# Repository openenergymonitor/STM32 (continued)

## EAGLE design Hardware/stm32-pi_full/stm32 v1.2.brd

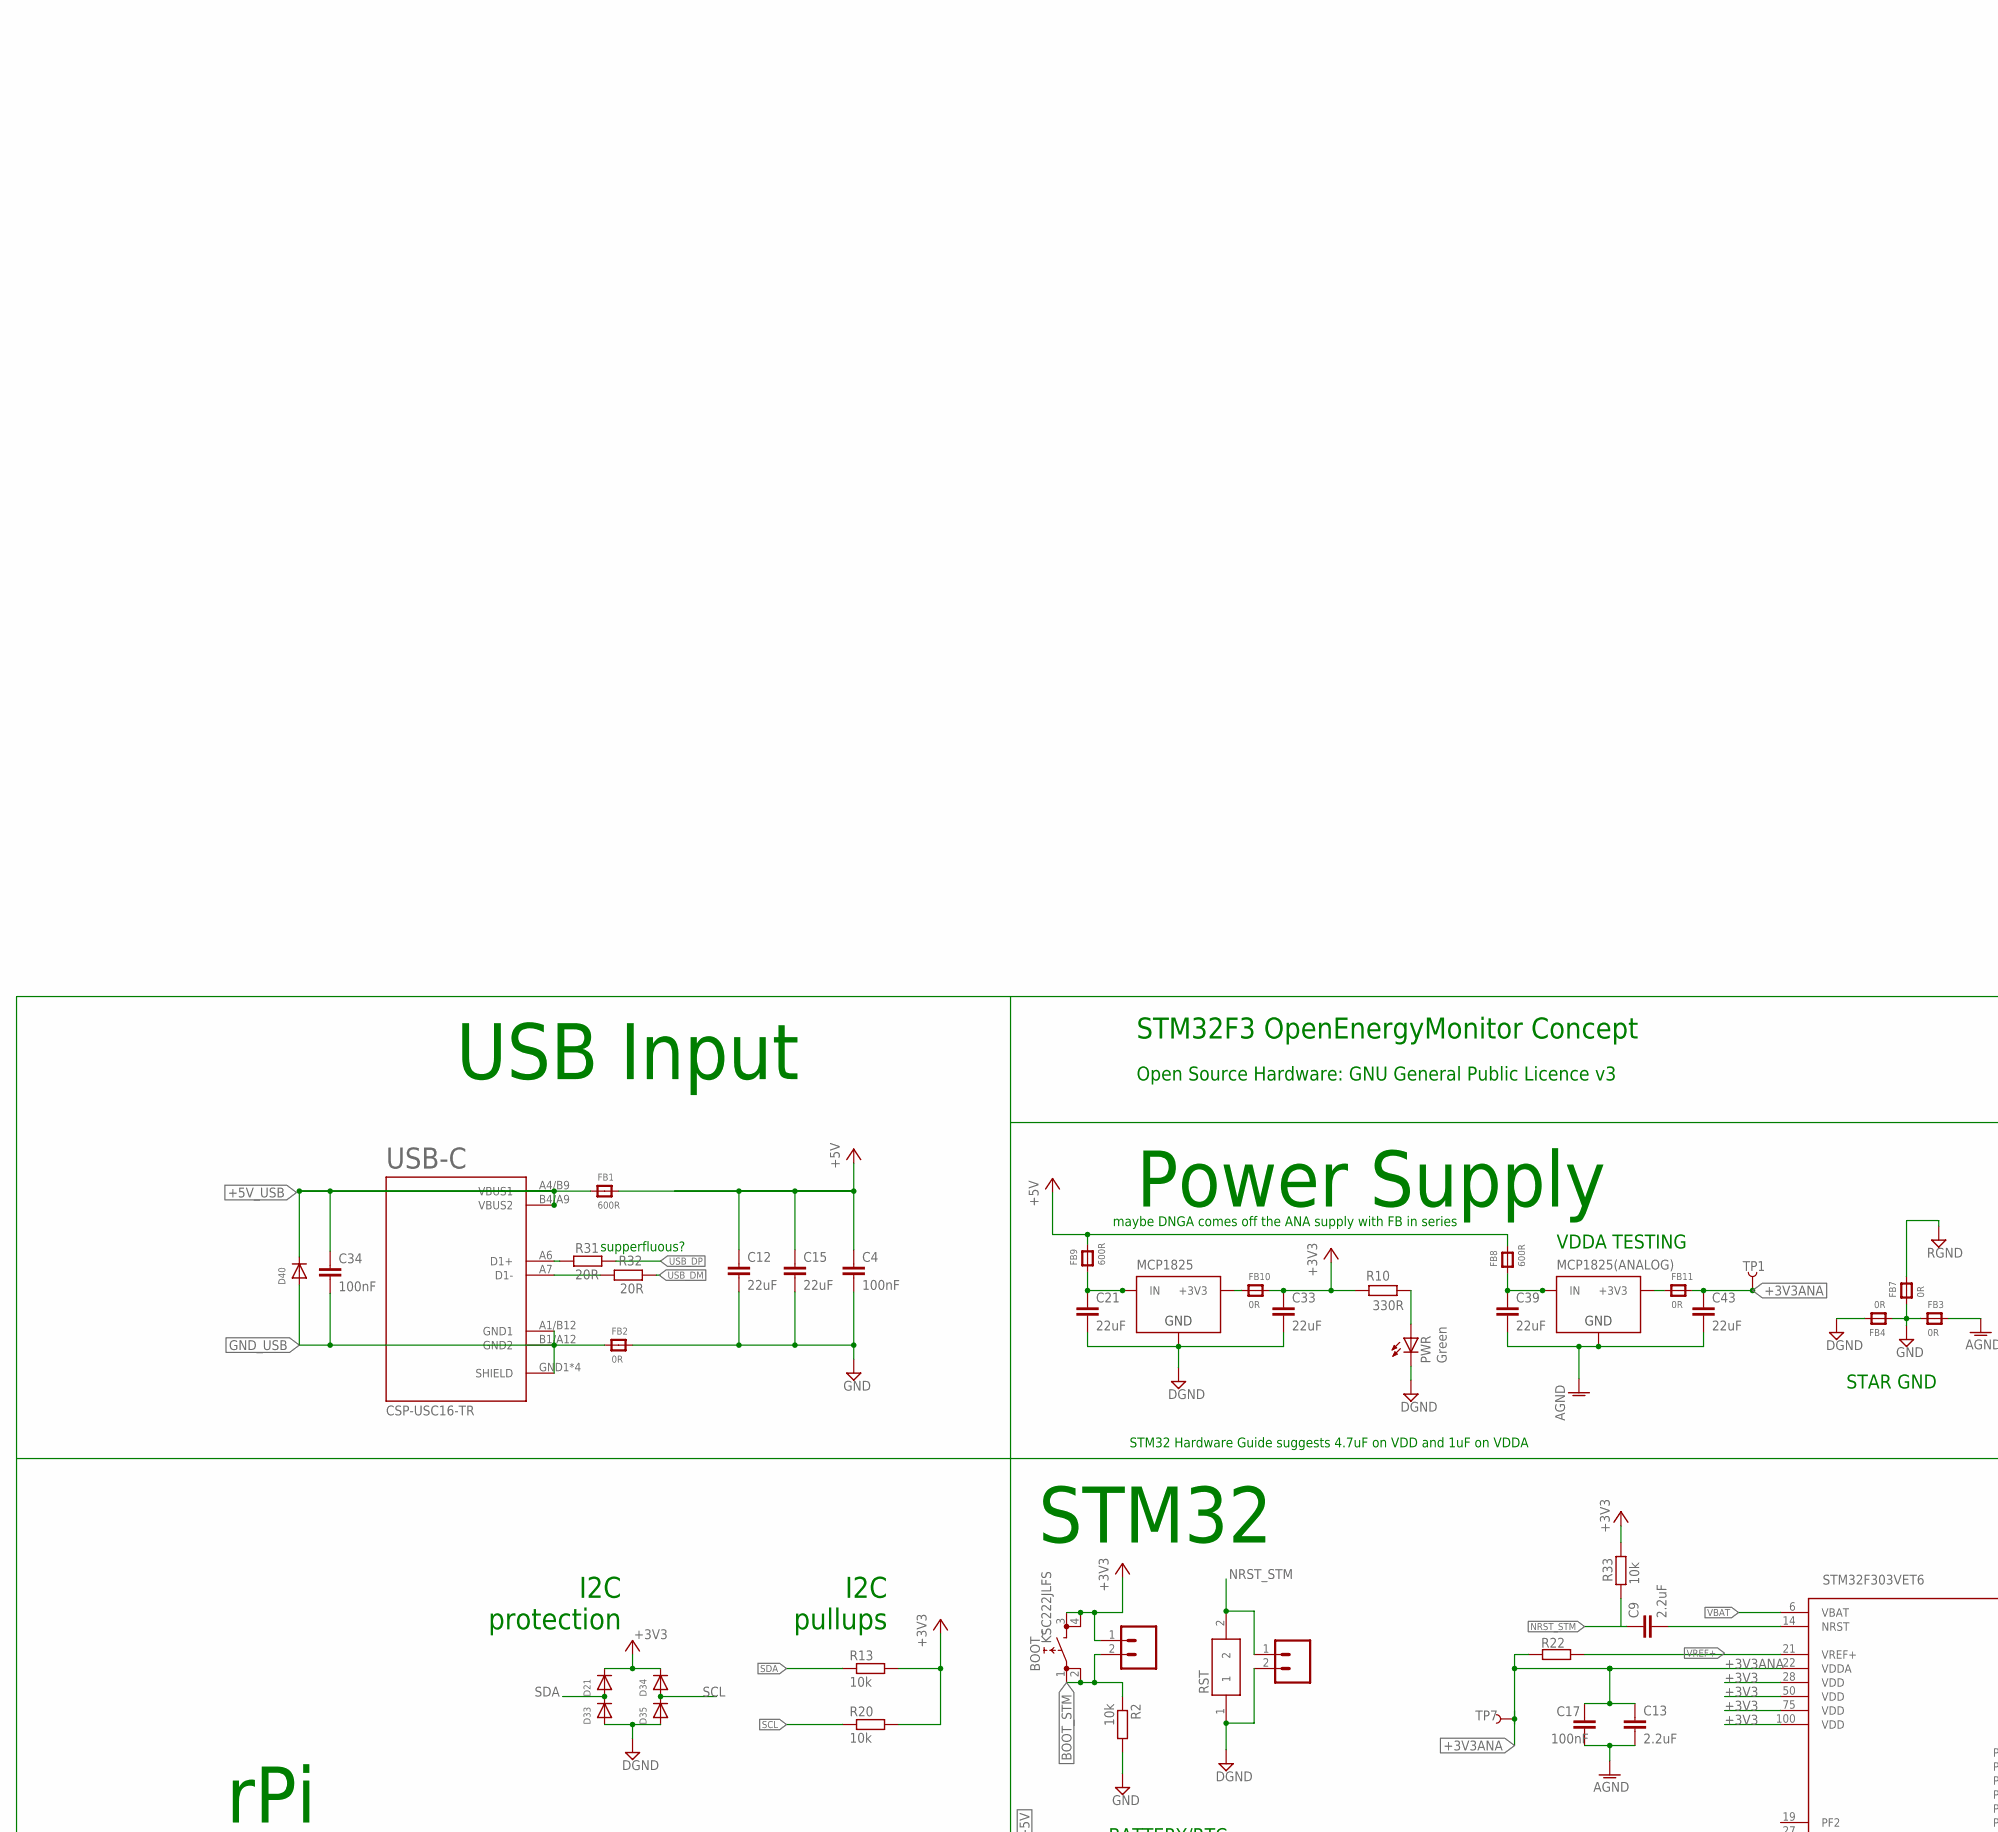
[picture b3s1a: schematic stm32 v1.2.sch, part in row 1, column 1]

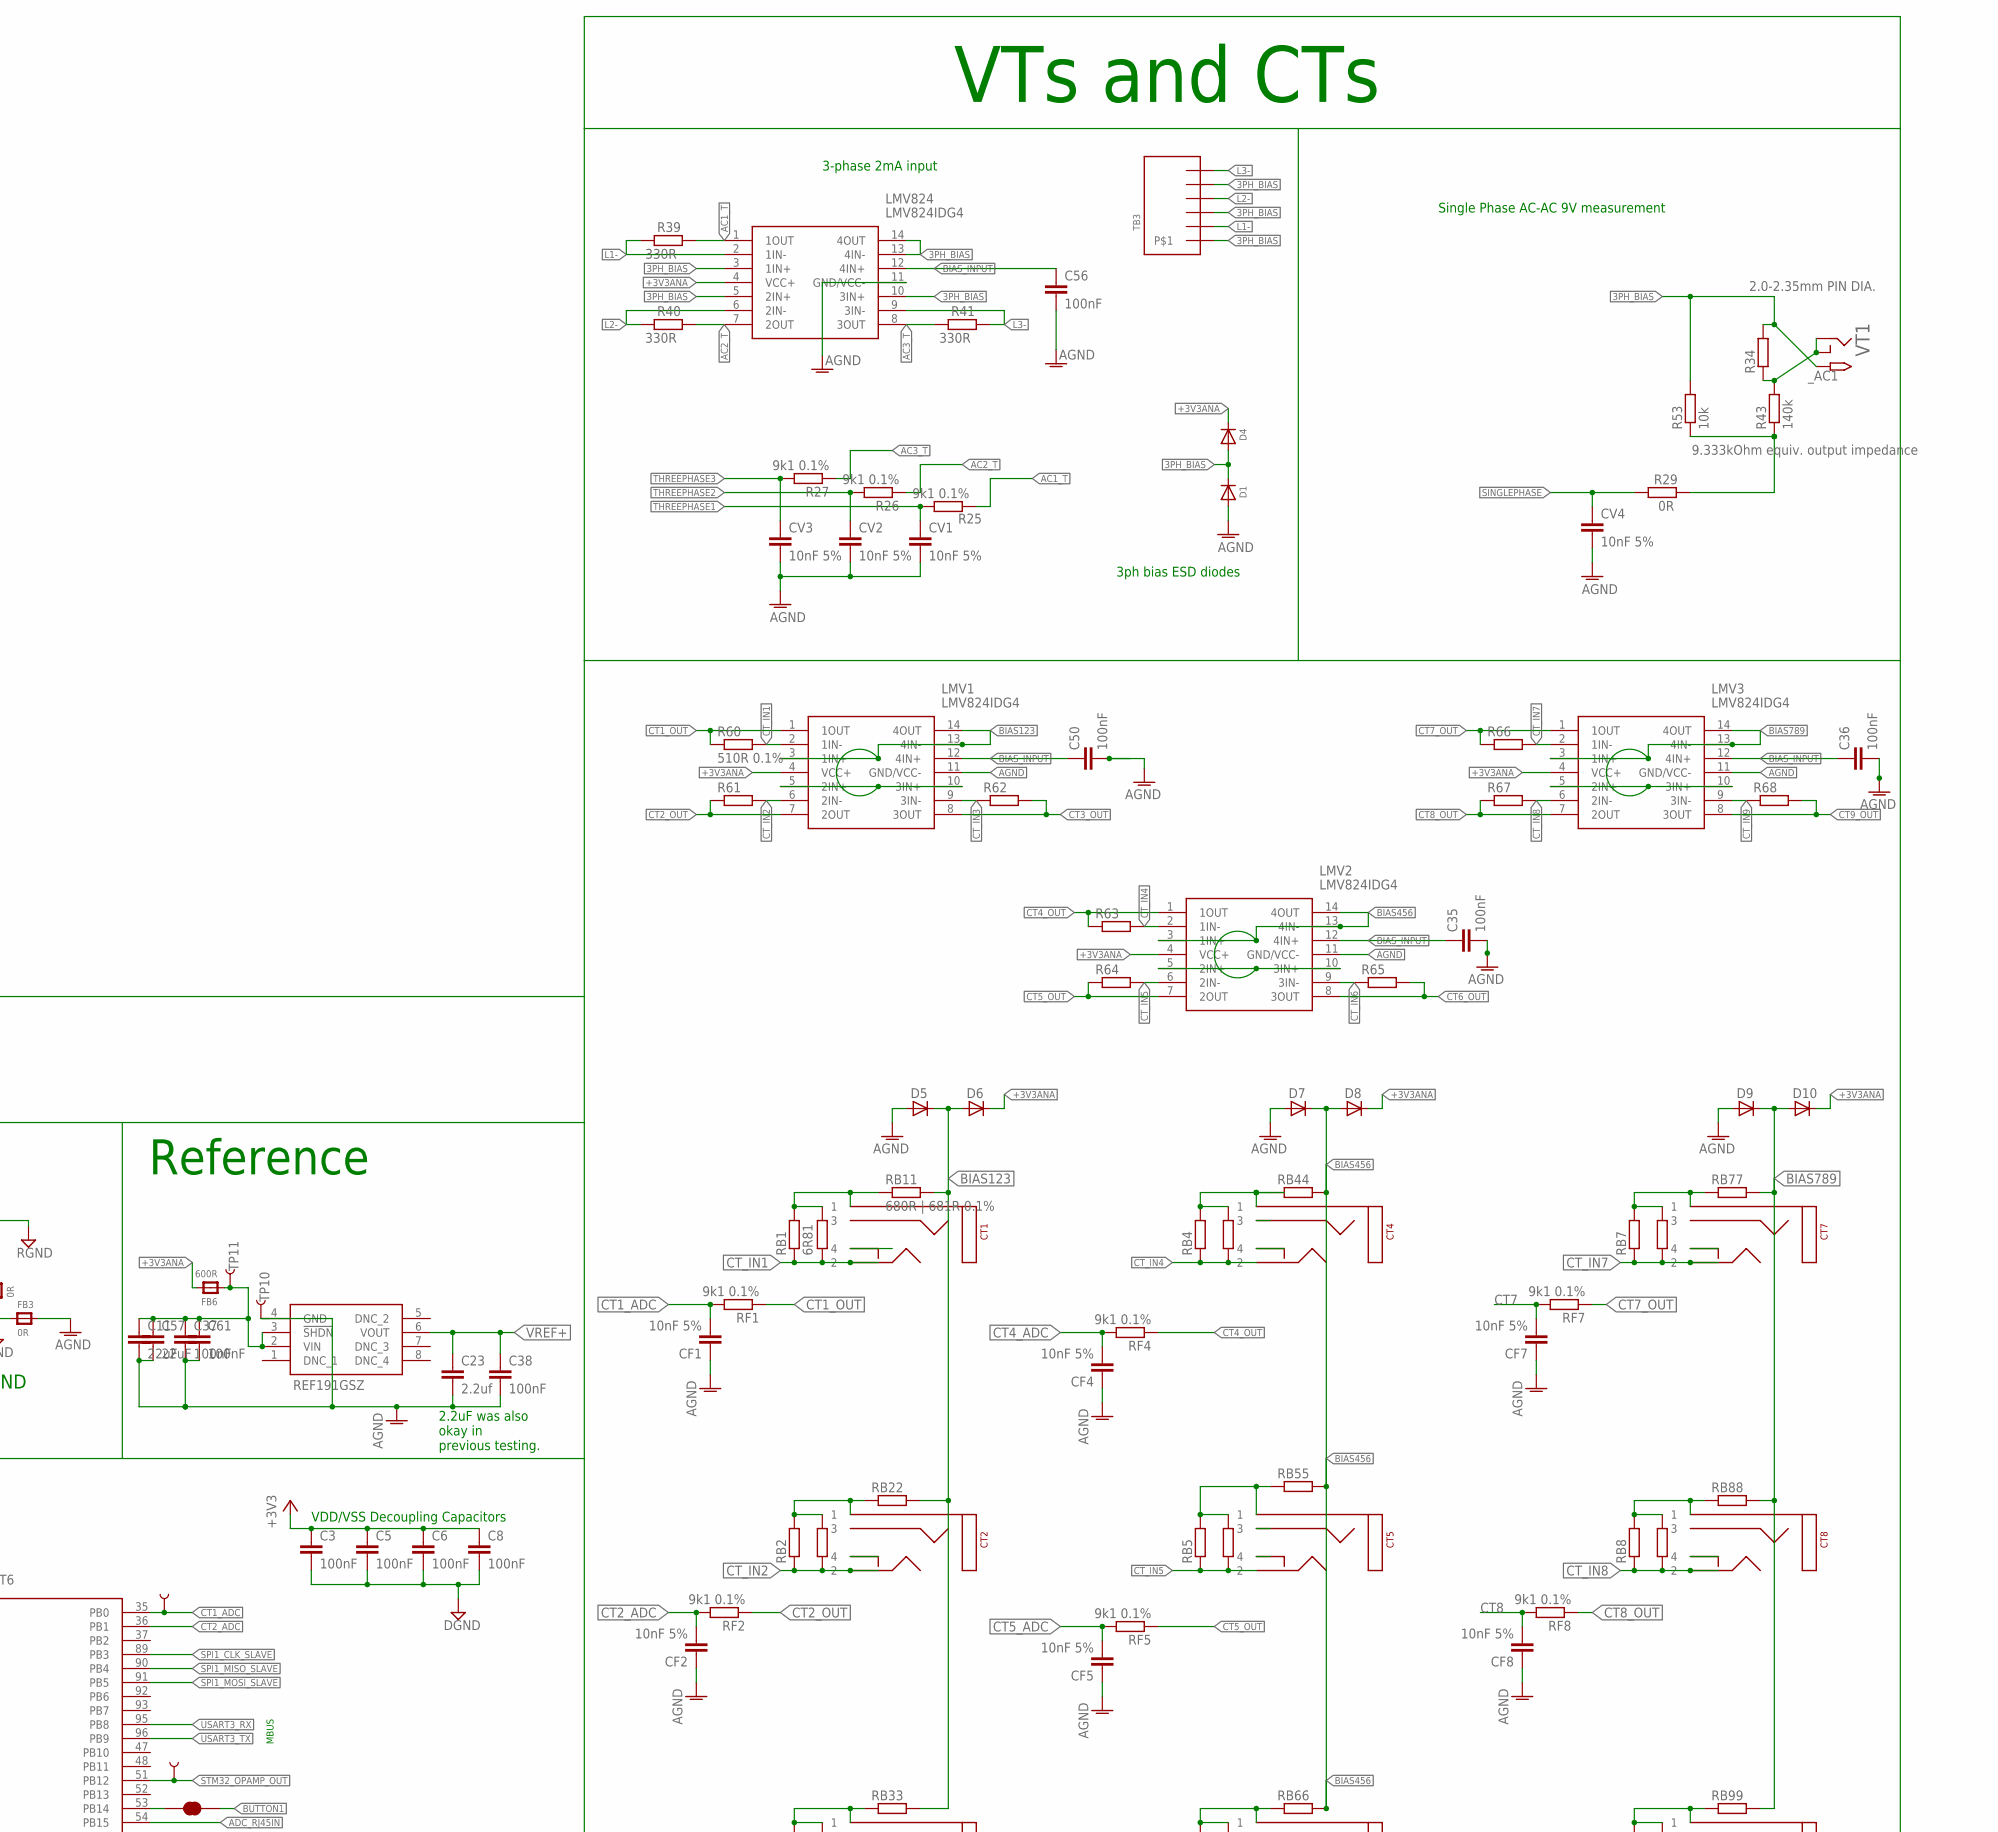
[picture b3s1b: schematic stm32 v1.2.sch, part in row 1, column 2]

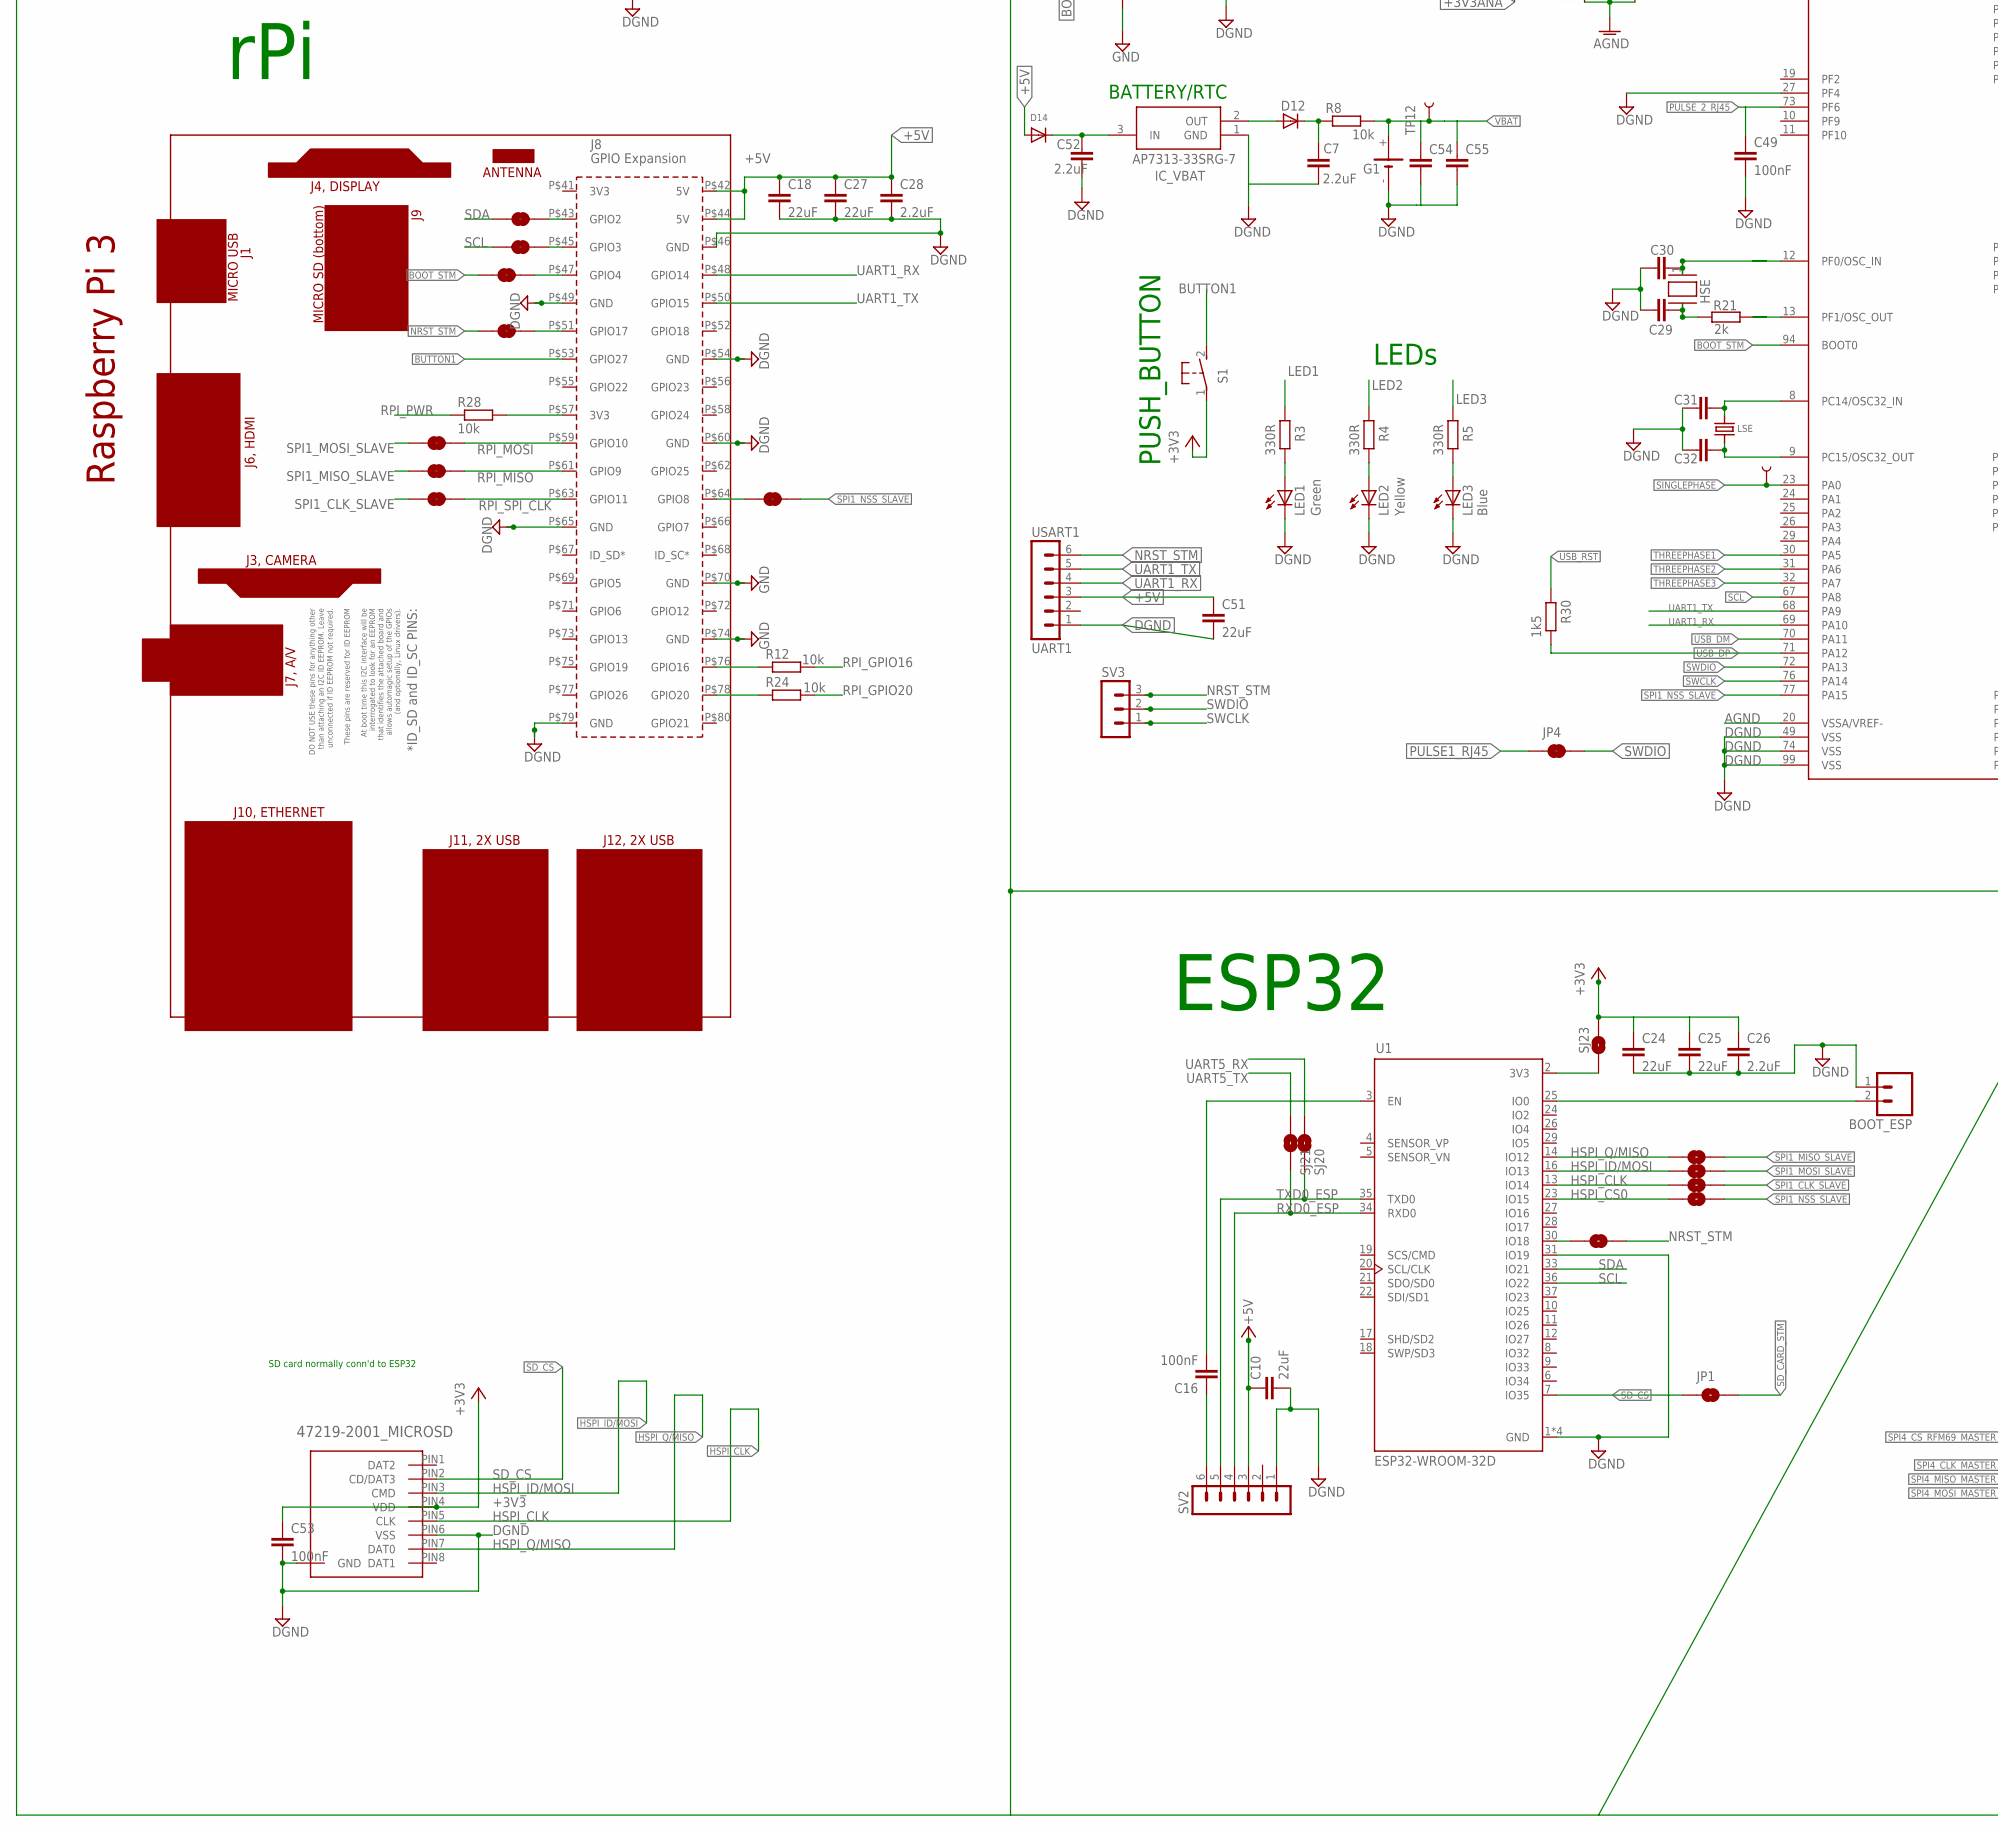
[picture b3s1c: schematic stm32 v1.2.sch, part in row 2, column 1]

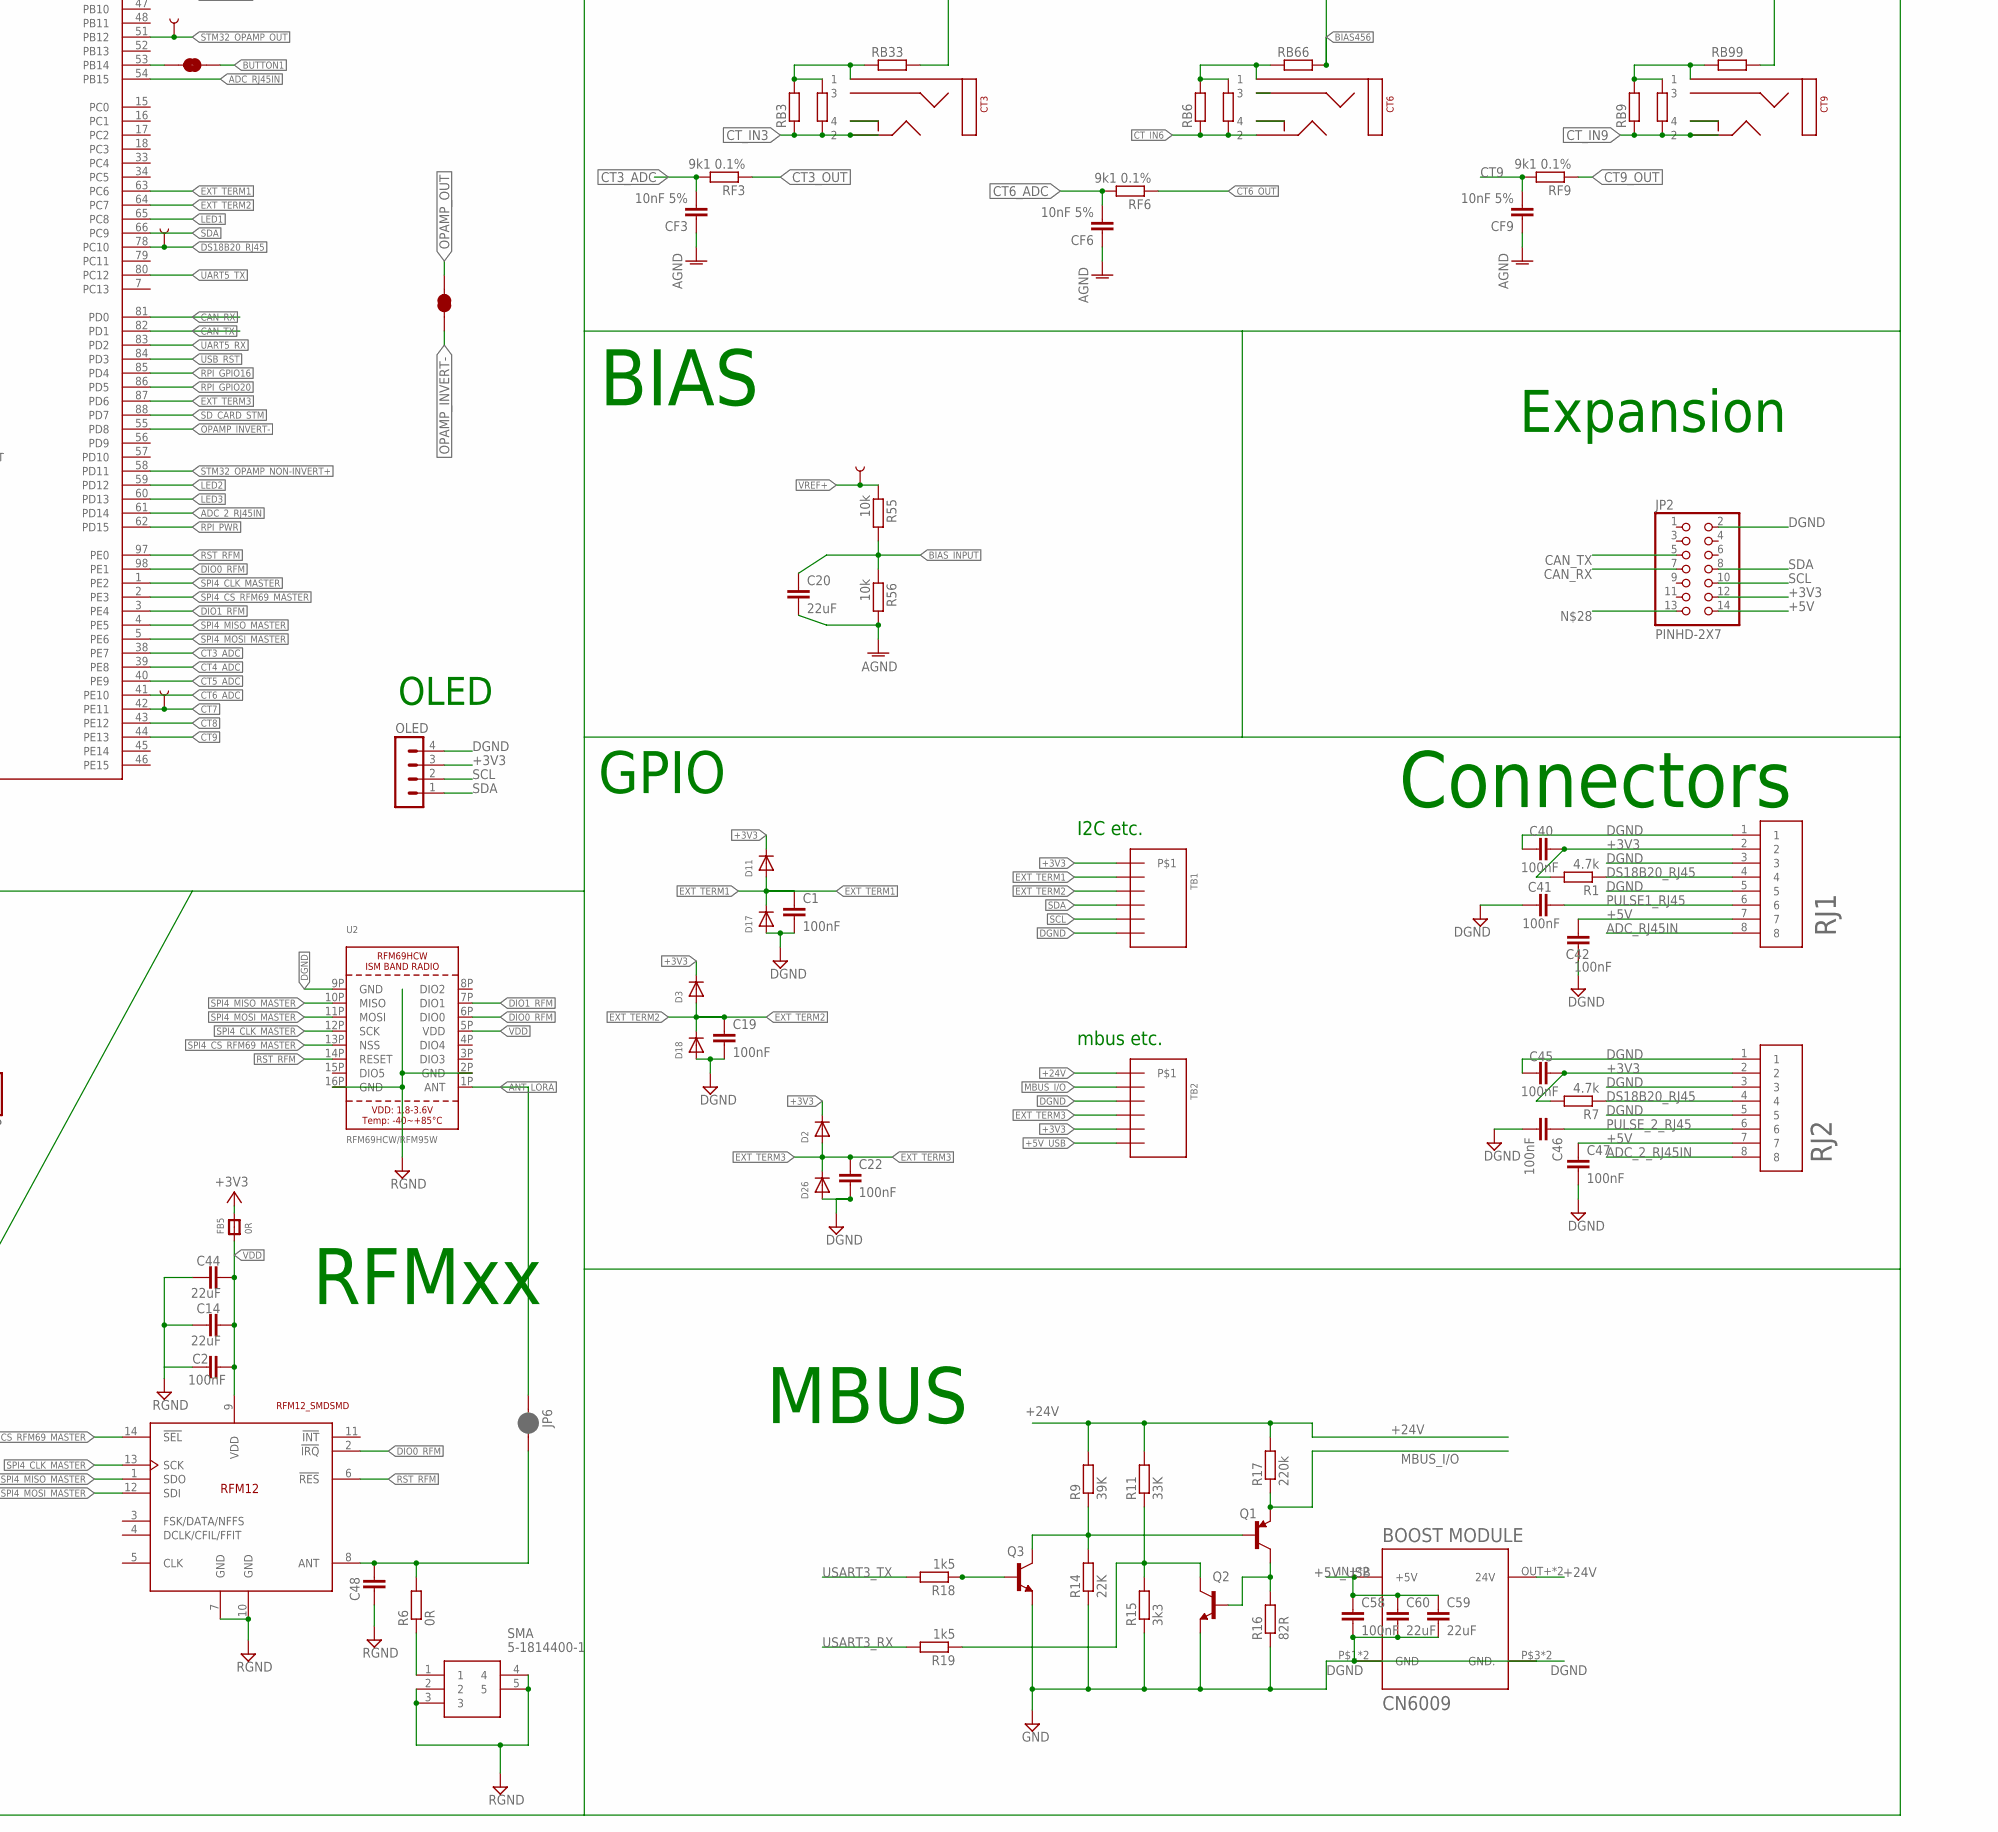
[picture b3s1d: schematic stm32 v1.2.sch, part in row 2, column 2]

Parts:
BOOT: M02PTH; 1X02
BOOT_: KSC222JLFS; MPN2 C318887
BOOT_ESP: M02PTH; 1X02
C1, C2, C3, C4, C5, C6, C8, C16, C17, C19, C22, C34, C35, C36, C37, C38, C40, C41, C42, C45, C46, C47, C49, C50, C53, C56, C58, C61: 100nF; C0603
C7, C9, C13, C26, C28, C52: 2.2uF; C0603
C10, C11, C12, C14, C15, C18, C20, C21, C24, C25, C27, C33, C39, C43, C44, C51, C54, C55, C57, C59, C60: 22uF; C0805
C23: 2.2uf; C0603
C29, C30: 15pF; C0603
C31, C32: 10pF; C0603
C48: C-EUC0603; C0603
CF1, CF2, CF3, CF4, CF5, CF6, CF7, CF8, CF9: 10nF 5%; C0805
CT1, CT2, CT3, CT4, CT5, CT6, CT7, CT8, CT9: SJ-3523-SMT; SJ-352X-SMT; MPN SJ-3523-SMT
CV1, CV2, CV3, CV4: 10nF 5%; C0805
D1, D4: DIODESOD-523; SOD-523; MPN PESD3V3S1UB
D2, D3, D11, D14, D17, D18, D21, D26, D33, D34, D35: ESD5Z3.3T1G; SOD-523
D5, D6, D7, D8, D9, D10, D12: DIODESOD-523; SOD-523
D40: ESD5Z5.0T1G; SOD-523
FB1: 600R; 0603; MPN MH1608-601Y
FB2: 0R; 0603; MPN MH1608-601Y
FB3, FB4, FB7: 0R; _0603
FB5, FB10, FB11: 0R; _0603; MPN BLM18BD252SN1D
FB6, FB8, FB9: 600R; _0603; MPN BLM18BD252SN1D
G1: CH291-1220LF
HSE: 6MM_3.5MM_CRYSTAL; ABMM2; MPN X50328MSD4SC
IC_VBAT: AP7313-33SRG-7; SOT96P240X135-3N; MPN AP7313-33SRG-7
J1: JUMPER-SMT_2_NC_TRACE_NO-SILK; SMT-JUMPER_2_NC_TRACE_NO-SILK
JP1: JUMPER-SMT_2_NO_NO-SILK; SMT-JUMPER_2_NO_NO-SILK
JP2: PINHD-2X7; 2X07
JP4: JUMPER-SMT_2_NC_TRACE_NO-SILK; SMT-JUMPER_2_NC_TRACE_NO-SILK
JP6: JUMPER-SMT_2_NC_PASTE_SILK; SMT-JUMPER_2_NC_PASTE_SILK
LED1: Green; CHIP-LED0805; MPN C2297
LED2: Yellow; CHIP-LED0805; MPN C2296
LED3: Blue; CHIP-LED0805; MPN C2293
LMV1, LMV2, LMV3, LMV824: LMV824IDG4; SOIC127P600X175-14N
LSE: 32.768kHz; CRYSTAL_8X3.8; MPN ABS25-32.768KHZ-T
MCP1825, MCP1825(ANALOG): MCP1825SOT-223-3; SOT-223
MICROSD: 47219-2001_MICROSD
OLED: MA04-1-OLEDOLED; MA04-1-OLED
PCB2: RPI3YA; RPI3MIRROR2; MPN M20-7872042
PWR: Green; CHIP-LED0805; MPN C2297
Q1: PNP; SOT23-R; MPN SMMBT3906LT1G
Q2, Q3: NPN; SOT23-R; MPN KST3904MTF
R1, R7: 4.7k; R0603
R2, R8, R12, R13, R20, R24, R28, R33, R53, R55, R56: 10k; R0603
R3, R4, R5, R10, R39, R40, R41: 330R; R0603
R6, R29: 0R; R0603
R9: 39K; R0603
R11: 33K; R0603
R14: 22K; R0603
R15: 3k3; R0603
R16: 82R; R0603
R17: 220k; R0603
R18, R19, R30: 1k5; R0603
R21: 2k; R0603
R22: R-EU_R0603; R0603
R25, R26, R27: 9k1 0.1%; R0603
R31, R32: 20R; R0603
R34: R-EU_R1210; R1210
R43: 140k; R0603
R60, R61, R62, R63, R64, R65, R66, R67, R68: 510R 0.1%; R0603
RB1, RB2, RB3, RB4, RB5, RB6, RB7, RB8, RB9: 6R81; R0805
RB1_, RB2_, RB3_, RB4_, RB5_, RB6_, RB7_, RB8_, RB9_: R-EU_0207/10; 0207/10
RB11, RB22, RB33, RB44, RB55, RB66, RB77, RB88, RB99: 680R | 681R 0.1%; R0603
REF19X: REF191ESZ; SOIC127P599X175-8N; MPN REF191GSZ
RF1, RF2, RF3, RF4, RF5, RF6, RF7, RF8, RF9: 9k1 0.1%; R0603
RFM69HCW: RFM12_SMDSMD; RFM12
RJ1, RJ2: 95501-6889; 955016889
RST: KSS221GLFS; KSS; MPN KSS331GLFS
RST_STM: M02PTH; 1X02
S1: 31-XX; B3F-31XX; MPN CST06S08H
SJ1, SJ3, SJ5, SJ6, SJ7, SJ14, SJ26, SJ27, SJ32: JUMPER-SMT_2_NC_TRACE_NO-SILK; SMT-JUMPER_2_NC_TRACE_NO-SILK
SJ4, SJ9, SJ10, SJ13: JUMPER-SMT_2_NO_SILK; SMT-JUMPER_2_NO_SILK
SJ20, SJ21, SJ23, SJ25: SOLDERJUMPERNO; SJ_2S-NO
SMA: 5-1814400-1; 518144001
STM32F303VET6: STM32F303VE; TQFP100
SV2: MA06-1
SV3: MA03-1
TB1, TB2, TB3: 3.5MM_TB_X6; 3.5MM_X6
TP1, TP2, TP7, TP8, TP9, TP10, TP11, TP18, TP19, TP20: TEST-POINTPOGO_PTH; 1X01_NO_SILK
TP12: TEST-POINT3; PAD.03X.03
U1: ESP32-WROOM-32D; MODULE_ESP32-WROOM-32D
U2: RFM69HCW/RFM95W; RFMHCW_SMT
U$2: BOOST_MODULEBOTHCONN; BOOST
USART1: UART1; MA06-1
USB-C: CSP-USC16-TR; USB-C
VT1: ADC-028-1-T; DCJACK_2MM_SMT; MPN PJ-002AH-SMT-TR

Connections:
3PH_BIAS: D1.K (C), D4.A, LMV824.3 (1IN+), LMV824.5 (2IN+), LMV824.10 (3IN+), LMV824.13 (4IN-), LMV824.14 (4OUT), R34.2, R53.2, TB3.P$1, TB3.P$3, TB3.P$5, VT1.PWR2 (TIP)
+3V3: BOOT.1, BOOT_.3, BOOT_.4, C3.1, C5.1, C6.1, C8.1, C24.1, C25.1, C26.1, C33.1, C40.1, C45.1, C53.1, D2.K (C), D3.K (C), D11.K (C), D21.K (C), D34.K (C), FB5.2, FB10.2, JP2.12, MICROSD.PIN4 (VDD), OLED.3, R1.2, R7.2, R10.2, R13.2, R20.2, R33.1, RJ1.2, RJ2.2, S1.1, SJ23.2, STM32F303VET6.28 (VDD), STM32F303VET6.50 (VDD), STM32F303VET6.75 (VDD), STM32F303VET6.100 (VDD), TB1.P$1, TB2.P$5
+3V3ANA: C13.1, C17.1, C43.1, D4.K (C), D6.K (C), D8.K (C), D10.K (C), FB6.2, FB11.2, LMV1.4 (VCC+), LMV2.4 (VCC+), LMV3.4 (VCC+), LMV824.4 (VCC+), R22.1, STM32F303VET6.22 (VDDA), TP1.1, TP7.1
+5V: C4.1, C10.1, C12.1, C15.1, C18.1, C27.1, C28.1, C42.1, C47.1, C51.1, D14.A, FB1.2, FB8.2, FB9.2, JP2.14, PCB2.P$42 (5V), PCB2.P$44 (5V), RJ1.7, RJ2.7, SV2.3, USART1.3
+5V_A: C39.1, FB8.1, MCP1825(ANALOG).1 (IN)
+5V_BATT: C52.1, D14.K (C), IC_VBAT.3 (IN)
+5V_D: C21.1, FB9.1, MCP1825.1 (IN)
+5V_USB: C34.1, C58.1, C59.1, C60.1, D40.K (C), FB1.1, TB2.P$6, U$2.IN+ (+5V), U$2.IN+1 (+5V), USB-C.A4/B9 (VBUS1), USB-C.B4/A9 (VBUS2)
+24V: R9.2, R11.2, R17.2, TB2.P$1, U$2.OUT+ (24V), U$2.OUT+1 (24V)
AC1: R29.1, R43.1, R53.1
AC1_T: LMV824.1 (1OUT), R25.1, R39.1
AC2_T: LMV824.7 (2OUT), R26.1, R40.1
AC3_T: LMV824.8 (3OUT), R27.1, R41.2
ADC_2_RJ45IN: RJ2.8, STM32F303VET6.61 (PD14)
ADC_RJ45IN: RJ1.8, STM32F303VET6.54 (PB15)
AGND: C11.2, C13.2, C17.2, C20.2, C23.2, C35.2, C36.2, C37.2, C38.2, C39.2, C43.2, C50.2, C56.2, C57.2, C61.2, CF1.1, CF2.1, CF3.1, CF4.1, CF5.1, CF6.1, CF7.1, CF8.1, CF9.1, CV1.2, CV2.2, CV3.2, CV4.2, D1.A, D5.A, D7.A, D9.A, FB3.2, LMV1.11 (GND/VCC-), LMV2.11 (GND/VCC-), LMV3.11 (GND/VCC-), LMV824.11 (GND/VCC-), MCP1825(ANALOG).2 (GND), MCP1825(ANALOG).4 (GND), R56.1, REF19X.4 (GND), STM32F303VET6.20 (VSSA/VREF-), TP10.1
ANT: C48.1, JP6.2, R6.2, RFM69HCW.8 (ANT)
ANT_LORA: JP6.1, U2.1P (ANT)
BIAS123: D5.K (C), D6.A, LMV1.3 (1IN+), LMV1.5 (2IN+), LMV1.10 (3IN+), LMV1.13 (4IN-), LMV1.14 (4OUT), RB11.2, RB22.2, RB33.2
BIAS456: D7.K (C), D8.A, LMV2.3 (1IN+), LMV2.5 (2IN+), LMV2.10 (3IN+), LMV2.13 (4IN-), LMV2.14 (4OUT), RB44.2, RB55.2, RB66.2
BIAS789: D9.K (C), D10.A, LMV3.3 (1IN+), LMV3.5 (2IN+), LMV3.10 (3IN+), LMV3.13 (4IN-), LMV3.14 (4OUT), RB77.2, RB88.2, RB99.2
BIAS_INPUT: C20.1, C35.1, C36.1, C50.1, C56.1, LMV1.12 (4IN+), LMV2.12 (4IN+), LMV3.12 (4IN+), LMV824.12 (4IN+), R55.1, R56.2
BOOT0_RPI: J1.2, PCB2.P$47 (GPIO4)
BOOT_STM: BOOT.2, BOOT_.1, BOOT_.2, J1.1, R2.1, STM32F303VET6.94 (BOOT0)
BUTTON1: PCB2.P$53 (GPIO27), S1.2 (S), SJ3.1
BUTTON1_STM: SJ3.2, STM32F303VET6.53 (PB14)
CAN_RX: JP2.7, STM32F303VET6.81 (PD0)
CAN_TX: JP2.5, STM32F303VET6.82 (PD1)
CT1_ADC: CF1.2, RF1.2, STM32F303VET6.35 (PB0), TP18.1
CT1_OUT: LMV1.1 (1OUT), R60.1, RF1.1
CT2_ADC: CF2.2, RF2.2, STM32F303VET6.36 (PB1)
CT2_OUT: LMV1.7 (2OUT), R61.1, RF2.1
CT3_ADC: CF3.2, RF3.2, STM32F303VET6.38 (PE7)
CT3_OUT: LMV1.8 (3OUT), R62.2, RF3.1
CT4_ADC: CF4.2, RF4.2, STM32F303VET6.39 (PE8)
CT4_OUT: LMV2.1 (1OUT), R63.1, RF4.1
CT5_ADC: CF5.2, RF5.2, STM32F303VET6.40 (PE9)
CT5_OUT: LMV2.7 (2OUT), R64.1, RF5.1
CT6_ADC: CF6.2, RF6.2, STM32F303VET6.41 (PE10)
CT6_OUT: LMV2.8 (3OUT), R65.2, RF6.1
CT7: CF7.2, RF7.2, STM32F303VET6.42 (PE11), TP19.1
CT7_OUT: LMV3.1 (1OUT), R66.1, RF7.1
CT8: CF8.2, RF8.2, STM32F303VET6.43 (PE12)
CT8_OUT: LMV3.7 (2OUT), R67.1, RF8.1
CT9: CF9.2, RF9.2, STM32F303VET6.44 (PE13)
CT9_OUT: LMV3.8 (3OUT), R68.2, RF9.1
CT_IN1: CT1.P$2 (2), LMV1.2 (1IN-), R60.2, RB1.1, RB1_.1
CT_IN2: CT2.P$2 (2), LMV1.6 (2IN-), R61.2, RB2.1, RB2_.1
CT_IN3: CT3.P$2 (2), LMV1.9 (3IN-), R62.1, RB3.1, RB3_.1
CT_IN4: CT4.P$2 (2), LMV2.2 (1IN-), R63.2, RB4.1, RB4_.1
CT_IN5: CT5.P$2 (2), LMV2.6 (2IN-), R64.2, RB5.1, RB5_.1
CT_IN6: CT6.P$2 (2), LMV2.9 (3IN-), R65.1, RB6.1, RB6_.1
CT_IN7: CT7.P$2 (2), LMV3.2 (1IN-), R66.2, RB7.1, RB7_.1
CT_IN8: CT8.P$2 (2), LMV3.6 (2IN-), R67.2, RB8.1, RB8_.1
CT_IN9: CT9.P$2 (2), LMV3.9 (3IN-), R68.1, RB9.1, RB9_.1
DGND: BOOT_ESP.1, C1.2, C3.2, C5.2, C6.2, C7.2, C8.2, C10.2, C18.2, C19.2, C21.2, C22.2, C24.2, C25.2, C26.2, C27.2, C28.2, C29.2, C30.2, C31.2, C32.2, C33.2, C40.2, C41.2, C42.2, C45.2, C46.2, C47.2, C49.2, C51.2, C52.2, C53.2, C54.2, C55.2, C58.2, C59.2, C60.2, D17.A, D18.A, D26.A, D33.A, D35.A, FB4.2, G1.-, IC_VBAT.1 (GND), JP2.2, LED1.C, LED2.C, LED3.C, MCP1825.2 (GND), MCP1825.4 (GND), MICROSD.P$1 (GND), MICROSD.P$2 (GND), MICROSD.P$3 (GND), MICROSD.P$4 (GND), MICROSD.PIN6 (VSS), OLED.4, PCB2.P$46 (GND), PCB2.P$49 (GND), PCB2.P$54 (GND), PCB2.P$60 (GND), PCB2.P$65 (GND), PCB2.P$70 (GND), PCB2.P$74 (GND), PCB2.P$79 (GND), PWR.C, Q2.2 (E), Q3.2 (E), R2.2, R14.1, R15.1, R16.1, RJ1.1, RJ1.3, RJ1.5, RJ2.1, RJ2.3, RJ2.5, RST.1, RST_STM.2, STM32F303VET6.27 (PF4), STM32F303VET6.49 (VSS), STM32F303VET6.74 (VSS), STM32F303VET6.99 (VSS), SV2.1, TB1.P$6, TB2.P$3, U1.1 (GND), U1.15 (GND), U1.31 (IO19), U1.38 (GND), U1.39 (GND), U2.9P (GND), U$2.P$1 (GND), U$2.P$2 (GND)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
DIO0_RFM: RFM69HCW.2 (!IRQ), STM32F303VET6.98 (PE1), U2.6P (DIO0)
DIO1_RFM: STM32F303VET6.3 (PE4), U2.7P (DIO1)
DS18B20_RJ45: R1.1, R7.1, RJ1.4, RJ2.4, STM32F303VET6.78 (PC10), TP9.1
ESP_PWR_PRE: SJ23.1, U1.2 (3V3)
EXT_TERM1: C1.1, D11.A, D17.K (C), STM32F303VET6.63 (PC6), TB1.P$2
EXT_TERM2: C19.1, D3.A, D18.K (C), STM32F303VET6.64 (PC7), TB1.P$3
EXT_TERM3: C22.1, D2.A, D26.K (C), STM32F303VET6.87 (PD6), TB2.P$4
GND: C4.2, C12.2, C15.2, FB2.2, FB3.1, FB4.1, FB7.1
GND_USB: C34.2, D40.A, FB2.1, USB-C.A1/B12 (GND1), USB-C.B1/A12 (GND2), USB-C.GND1 (SHIELD), USB-C.GND2 (SHIELD), USB-C.GND3 (SHIELD), USB-C.GND4 (SHIELD)
HSE_IN: C30.1, HSE.1 (CRYSTAL_1), STM32F303VET6.12 (PF0/OSC_IN)
HSE_OUT: R21.1, STM32F303VET6.13 (PF1/OSC_OUT)
HSE_OUT_: C29.1, HSE.3 (CRYSTAL_2), R21.2
HSPI_CLK: MICROSD.PIN5 (CLK), SJ10.1, U1.13 (IO14)
HSPI_CS0: SJ13.1, U1.23 (IO15)
HSPI_ID/MOSI: MICROSD.PIN3 (CMD), SJ9.1, U1.16 (IO13)
HSPI_Q/MISO: MICROSD.PIN7 (DAT0), SJ4.1, U1.14 (IO12)
L1-: LMV824.2 (1IN-), R39.2, TB3.P$2
L2-: LMV824.6 (2IN-), R40.2, TB3.P$4
L3-: LMV824.9 (3IN-), R41.1, TB3.P$6
LED1: R3.2, STM32F303VET6.65 (PC8)
LED2: R4.2, STM32F303VET6.59 (PD12)
LED3: R5.2, STM32F303VET6.60 (PD13)
MBUS_I/O: Q1.2 (E), R17.1, TB2.P$2
unnamed: LED2.A, R4.1
unnamed: LED3.A, R5.1
unnamed: CT5.P$1 (1), RB5.2, RB5_.2, RB55.1
unnamed: PWR.A, R10.1
unnamed: PCB2.P$64 (GPIO8), SJ14.1
unnamed: C16.1, SV2.6
unnamed: C16.2, U1.3 (EN)
unnamed: C7.1, D12.K (C), R8.1
unnamed: BOOT_ESP.2, U1.25 (IO0)
unnamed: PCB2.P$57 (3V3), R28.2
unnamed: FB10.1, MCP1825.3 (+3V3)
unnamed: CT1.P$1 (1), RB1.2, RB1_.2, RB11.1
unnamed: CT2.P$1 (1), RB2.2, RB2_.2, RB22.1
unnamed: C11.1, C37.1, C57.1, C61.1, FB6.1, REF19X.2 (VIN), REF19X.3 (!SHDN), TP11.1
unnamed: Q1.3 (C), Q2.1 (B), R16.2
unnamed: Q1.1 (B), Q3.3 (C), R9.1, R14.2
unnamed: Q2.3 (C), R11.1, R15.2, R19.1
unnamed: Q3.1 (B), R18.1
unnamed: FB11.1, MCP1825(ANALOG).3 (+3V3)
unnamed: CT4.P$1 (1), RB4.2, RB4_.2, RB44.1
unnamed: CT3.P$1 (1), RB3.2, RB3_.2, RB33.1
unnamed: R6.1, SMA.1
unnamed: CT6.P$1 (1), RB6.2, RB6_.2, RB66.1
unnamed: LED1.A, R3.1
unnamed: CT9.P$1 (1), RB9.2, RB9_.2, RB99.1
unnamed: D12.A, IC_VBAT.2 (OUT)
unnamed: CT8.P$1 (1), RB8.2, RB8_.2, RB88.1
unnamed: CT7.P$1 (1), RB7.2, RB7_.2, RB77.1
NRST_STM: C9.1, R33.2, RST.2, RST_STM.1, SJ25.2, SJ32.1, SV3.3, USART1.6
NRST_STM_: C9.2, STM32F303VET6.14 (NRST)
NRST_STM_ESP: SJ25.1, U1.30 (IO18)
NRST_STM_RPI: PCB2.P$51 (GPIO17), SJ32.2
OPAMP_INVERT-: SJ1.1, STM32F303VET6.55 (PD8)
OPAMP_OUT: SJ1.2
PC14: C31.1, LSE.P$1 (1), STM32F303VET6.8 (PC14/OSC32_IN)
PC15: C32.1, LSE.P$4 (2), STM32F303VET6.9 (PC15/OSC32_OUT)
PULSE1_RJ45: C41.1, JP4.1, RJ1.6
PULSE_2_RJ45: C46.1, C49.1, RJ2.6, STM32F303VET6.73 (PF6)
RGND: C2.2, C14.2, C44.2, C48.2, FB7.2, RFM69HCW.7 (GND), RFM69HCW.10 (GND), SMA.2, SMA.3, SMA.4, SMA.5, U2.2P (GND), U2.16P (GND)
RPI_GPIO16: R12.2, STM32F303VET6.85 (PD4)
RPI_GPIO16_RPI: PCB2.P$76 (GPIO16), R12.1
RPI_GPIO20: R24.2, STM32F303VET6.86 (PD5)
RPI_GPIO20_RPI: PCB2.P$78 (GPIO20), R24.1
RPI_MISO: PCB2.P$61 (GPIO9), SJ6.2
RPI_MOSI: PCB2.P$59 (GPIO10), SJ5.2
RPI_PWR: R28.1, STM32F303VET6.62 (PD15)
RPI_SPI_CLK: PCB2.P$63 (GPIO11), SJ7.2
RST_RFM: RFM69HCW.6 (!RES), STM32F303VET6.97 (PE0), U2.14P (RESET)
RXD0_ESP: SJ21.2, SV2.4, U1.34 (RXD0)
SCL: D34.A, D35.K (C), JP2.10, OLED.2, R20.1, SJ27.2, STM32F303VET6.67 (PA8), TB1.P$5, U1.36 (IO22)
SCL_: PCB2.P$45 (GPIO3), SJ27.1
SDA: D21.A, D33.K (C), JP2.8, OLED.1, R13.1, SJ26.1, STM32F303VET6.66 (PC9), TB1.P$4, U1.33 (IO21)
SDA_: PCB2.P$43 (GPIO2), SJ26.2
SD_CARD_STM: JP1.2, STM32F303VET6.88 (PD7)
SD_CS: JP1.1, MICROSD.PIN2 (CD/DAT3), U1.7 (IO35)
SINGLEPHASE: CV4.1, R29.2, STM32F303VET6.23 (PA0), TP20.1
SPI1_CLK_SLAVE: SJ7.1, SJ10.2, STM32F303VET6.89 (PB3)
SPI1_MISO_SLAVE: SJ4.2, SJ6.1, STM32F303VET6.90 (PB4)
SPI1_MOSI_SLAVE: SJ5.1, SJ9.2, STM32F303VET6.91 (PB5)
SPI1_NSS_SLAVE: SJ13.2, SJ14.2, STM32F303VET6.77 (PA15)
SPI4_CLK_MASTER: RFM69HCW.13 (SCK), STM32F303VET6.1 (PE2), U2.12P (SCK)
SPI4_CS_RFM69_MASTER: RFM69HCW.14 (!SEL), STM32F303VET6.2 (PE3), U2.13P (NSS)
SPI4_MISO_MASTER: RFM69HCW.1 (SDO), STM32F303VET6.4 (PE5), U2.10P (MISO)
SPI4_MOSI_MASTER: RFM69HCW.12 (SDI), STM32F303VET6.5 (PE6), U2.11P (MOSI)
STM32_OPAMP_NON-INVERT+: STM32F303VET6.58 (PD11)
STM32_OPAMP_OUT: STM32F303VET6.51 (PB12), TP2.1
SWCLK: STM32F303VET6.76 (PA14), SV3.1
SWDIO: JP4.2, STM32F303VET6.72 (PA13), SV3.2
THREEPHASE1: CV1.1, R25.2, STM32F303VET6.30 (PA5)
THREEPHASE2: CV2.1, R26.2, STM32F303VET6.31 (PA6)
THREEPHASE3: CV3.1, R27.2, STM32F303VET6.32 (PA7)
TXD0_ESP: SJ20.2, SV2.5, U1.35 (TXD0)
UART1_RX: PCB2.P$48 (GPIO14), STM32F303VET6.69 (PA10), USART1.4
UART1_TX: PCB2.P$50 (GPIO15), STM32F303VET6.68 (PA9), USART1.5
UART5_RX: SJ20.1, STM32F303VET6.83 (PD2)
UART5_TX: SJ21.1, STM32F303VET6.80 (PC12)
USART3_RX: R19.2, STM32F303VET6.95 (PB8)
USART3_TX: R18.2, STM32F303VET6.96 (PB9)
USB_DM: R32.2, STM32F303VET6.70 (PA11)
USB_DM_: R32.1, USB-C.A7 (D1-)
USB_DP: R30.1, R31.2, STM32F303VET6.71 (PA12)
USB_DP_: R31.1, USB-C.A6 (D1+)
USB_RST: R30.2, STM32F303VET6.84 (PD3)
VBAT: C54.1, C55.1, G1.+, R8.2, STM32F303VET6.6 (VBAT), TP12.P$1
VDD: C2.1, C14.1, C44.1, FB5.1, RFM69HCW.9 (VDD), U2.5P (VDD)
VREF+: C23.1, C38.1, R22.2, R55.2, REF19X.6 (VOUT), STM32F303VET6.21 (VREF+), TP8.1
_AC1: R34.1, R43.2, VT1.GND (RING), VT1.GNDBREAK (RING_SW)

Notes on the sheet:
VDD/VSS Decoupling Capacitors
Single Phase AC-AC 9V measurement
VTs and CTs
STM32F3 OpenEnergyMonitor Concept
Power Supply
STM32
Open Source Hardware: GNU General Public Licence v3
Reference
ESP32
MBUS
rPi
RFMxx
Connectors
Expansion
LEDs
PUSH_BUTTON
OLED
USB Input
BATTERY/RTC
I2C pullups
SD card normally conn'd to ESP32
VDDA TESTING
STAR GND
STM32 Hardware Guide suggests 4.7uF on VDD and 1uF on VDDA
supperfluous?
maybe DNGA comes off the ANA supply with FB in series
2.2uF was also okay in previous testing.
I2C protection
GPIO
mbus etc.
3-phase 2mA input
BIAS
3ph bias ESD diodes
I2C etc.
2.0-2.35mm PIN DIA.
9.333kOhm equiv. output impedance
